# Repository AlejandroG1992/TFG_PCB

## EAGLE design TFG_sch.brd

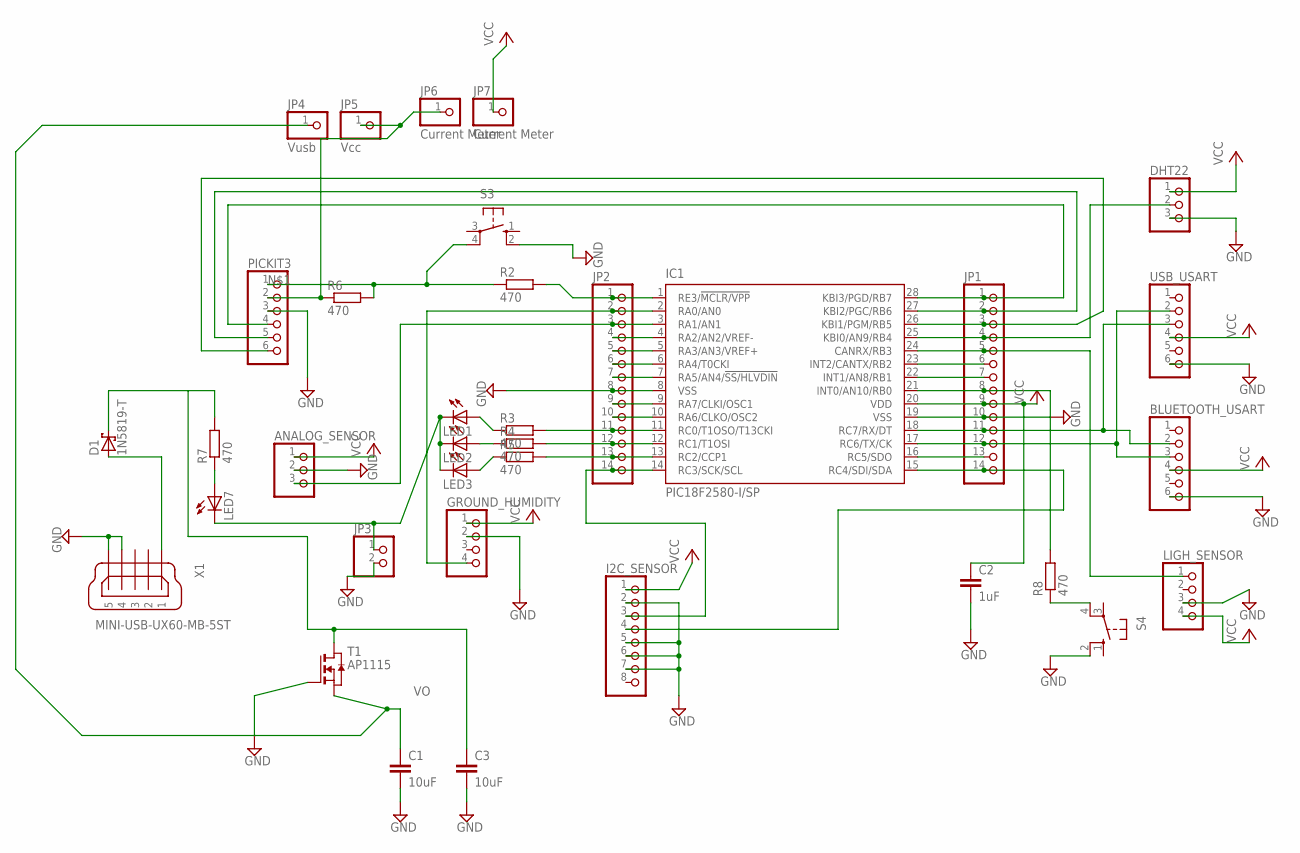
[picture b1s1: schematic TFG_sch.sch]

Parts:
ANALOG_SENSOR: PINHD-1X3; 1X03
BLUETOOTH_USART: PINHD-1X6; 1X06
C1, C3: 10uF; C1206
C2: 1uF; C1206
D1: 1N5819-T; DO41-7.6
DHT22: PINHD-1X3; 1X03
GROUND_HUMIDITY: PINHD-1X4; 1X04
I2C_SENSOR: PINHD-1X8; 1X08
IC1: PIC18F2580-I/SP; DIL28-3
JP1, JP2: PINHD-1X14; 1X14
JP3: PINHD-1X2; 1X02
JP4: Vusb; 1X01
JP5: Vcc; 1X01
JP6, JP7: Current Meter; 1X01
LED1, LED2, LED3, LED7: LED_E; LED_1206
LIGH_SENSOR: PINHD-1X4; 1X04
PICKIT3: PINHD-1X6/90; 1X06/90
R2, R3, R4, R5, R6, R7, R8: 470; R1206
S3, S4: 10-XX; B3F-10XX
T1: AP1115; SOT89
USB_USART: PINHD-1X6; 1X06
X1: MINI-USB-UX60-MB-5ST; UX60-MB-5ST

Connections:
GND: ANALOG_SENSOR.2, BLUETOOTH_USART.6, C1.2, C2.2, C3.2, DHT22.3, GROUND_HUMIDITY.2, I2C_SENSOR.2, I2C_SENSOR.5, I2C_SENSOR.6, I2C_SENSOR.7, IC1.8 (VSS), IC1.19 (VSS), JP1.10, JP2.8, JP3.2, LIGH_SENSOR.3, PICKIT3.3, S3.2 (S1), S4.2 (S1), T1.1 (G), USB_USART.6, X1.4, X1.5
unnamed: PICKIT3.1, R2.1, R6.2, S3.4 (P1)
unnamed: GROUND_HUMIDITY.4, IC1.2 (RA0/AN0), JP2.2
unnamed: ANALOG_SENSOR.3, IC1.3 (RA1/AN1), JP2.3
unnamed: IC1.4 (RA2/AN2/VREF-), JP2.4
unnamed: IC1.5 (RA3/AN3/VREF+), JP2.5
unnamed: IC1.6 (RA4/T0CKI), JP2.6
unnamed: IC1.7 (RA5/AN4/!SS/HLVDIN), JP2.7
unnamed: I2C_SENSOR.3, IC1.14 (RC3/SCK/SCL), JP2.14
unnamed: IC1.9 (RA7/CLKI/OSC1), JP2.9
unnamed: IC1.10 (RA6/CLKO/OSC2), JP2.10
unnamed: IC1.11 (RC0/T1OSO/T13CKI), JP2.11, R3.2
unnamed: IC1.12 (RC1/T1OSI), JP2.12, R4.2
unnamed: IC1.13 (RC2/CCP1), JP2.13, R5.2
unnamed: IC1.28 (KBI3/PGD/RB7), JP1.1, PICKIT3.4
unnamed: IC1.27 (KBI2/PGC/RB6), JP1.2, PICKIT3.5
unnamed: IC1.26 (KBI1/PGM/RB5), JP1.3
unnamed: DHT22.2, IC1.25 (KBI0/AN9/RB4), JP1.4
unnamed: IC1.24 (CANRX/RB3), JP1.5, LIGH_SENSOR.1
unnamed: IC1.23 (INT2/CANTX/RB2), JP1.6
unnamed: IC1.22 (INT1/AN8/RB1), JP1.7
unnamed: IC1.21 (INT0/AN10/RB0), JP1.8, R8.2
unnamed: IC1.1 (RE3/!MCLR/VPP), JP2.1, R2.2
unnamed: R8.1, S4.4 (P1)
unnamed: BLUETOOTH_USART.2, IC1.18 (RC7/RX/DT), JP1.11, USB_USART.3
unnamed: BLUETOOTH_USART.3, IC1.17 (RC6/TX/CK), JP1.12, USB_USART.2
unnamed: IC1.16 (RC5/SDO), JP1.13
unnamed: I2C_SENSOR.4, IC1.15 (RC4/SDI/SDA), JP1.14
unnamed: LED1.A, R3.1
unnamed: LED2.A, R4.1
unnamed: LED3.A, R5.1
unnamed: JP3.1, LED1.C, LED2.C, LED3.C, LED7.C
unnamed: LED7.A, R7.1
unnamed: D1.A, X1.1
unnamed: C3.1, D1.C, R7.2, T1.2 (D), T1.2@1 (D)
unnamed: JP5.1, JP6.1, PICKIT3.2, R6.1
VCC: ANALOG_SENSOR.1, BLUETOOTH_USART.4, C2.1, DHT22.1, GROUND_HUMIDITY.1, I2C_SENSOR.1, IC1.20 (VDD), JP1.9, JP7.1, LIGH_SENSOR.4, USB_USART.4
VO: C1.1, JP4.1, T1.3 (S)

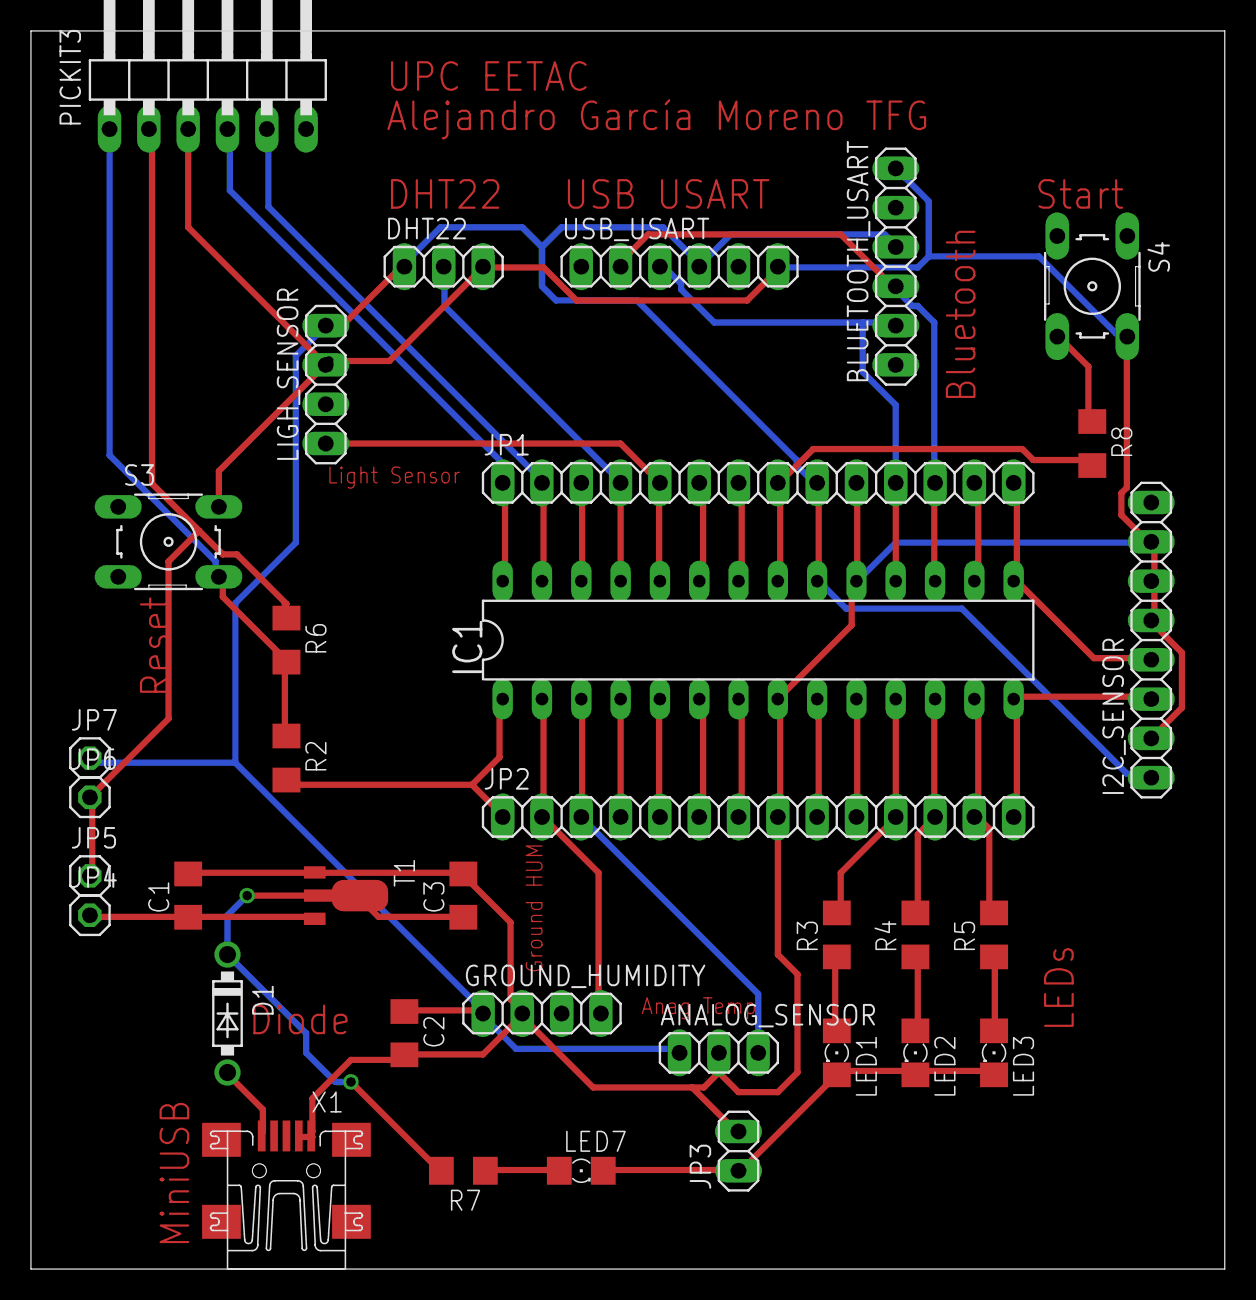
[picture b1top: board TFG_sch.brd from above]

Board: 2 copper layers, 77.1 x 80.0 mm, 35 parts (0 on the bottom side), 38 nets.

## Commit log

2016-03-29 :confetti_ball: Added .gitattributes & .gitignore files
2016-03-29 EAGLE PCB
2016-03-30 resistencias
2016-04-12 commsa
2016-05-02 comint
